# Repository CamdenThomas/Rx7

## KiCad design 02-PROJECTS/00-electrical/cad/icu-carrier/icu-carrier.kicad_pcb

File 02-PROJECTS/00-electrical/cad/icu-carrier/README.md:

# ICU carrier — the KiCad project

*Rev 2026-09-12 (rev 0.02 of the sheet) · owns: what this KiCad project is for, what it may
claim, and how to start. The board's design is `../../data/icu_channels.csv` — that is the
record; this is a drawing of it. Read `../README.md` first: it is the fence.*

## Where it stands

**The schematic is drawn, all five blocks, and ERC is clean at zero errors and zero
warnings** (re-run on the Fedora machine 2026-09-22, after J5 got its real pads and the 5 V buck
was drawn in full from TI's datasheet: U1 LMR36015FSCQ-Q1 with L2, C20–C26 and R41–R43, F13). The next
step is the beginner guide, `../PCB-AND-3D-GUIDE.md`, step 1. Power, bus, the nine analog channels plus the illumination reference, both
pulse inputs, and the display-and-local block. About 200 symbols, 95 named nets.

**It has already earned its keep.** The first pass had **every BAT54S clamp wired
backwards** — anode to +3V3 and cathode to ground instead of the other way round. Drawn
that way the clamp catches nothing on either polarity and puts a diode path from +3V3 to
ground straight through the sender. The prose the record carries — *"→ 100 nF → BAT54S to
3V3 / GND"* — is completely correct and completely silent about direction, which is the
argument for the drawing made in `../README.md`, arriving on the first attempt. It is
fixed, it is checked mechanically now, and the sheet says out loud which way round it goes
and why.

## Why it exists

1. **To learn KiCad on something real.** A tutorial board teaches the keystrokes and
   nothing else. This one is already specified down to the resistor values, so the design
   work is done and the only thing left to learn is the tool. Whatever comes next that
   needs a PCB, the practice is already paid for.
2. **Because the analog front end cannot be reviewed as prose.** See `../README.md`.

## What it may and may not claim

**May:** how the parts on the carrier connect to each other — divider ratios, clamp
placement, the pull-up jumpers, the comparator's hysteresis network, decoupling, what
shares a rail, and what the ERC thinks of all of it.

**May not:** anything about the car, the harness, or the drops. `DP-ICU-A 1` and
`DP-ICU-B 4` appear here only as pins on the board edge; what is on the other side of them
belongs to `cavities.csv`. **If this schematic and the record disagree, the record is
right.**

**Two things this revision deliberately does not assert, and says so on the sheet:**

- **The Teensy pinout — asserted since 2026-09-22.** D-377 put every channel's Teensy pin in
  `icu_channels.teensy_pin`, so `J5` now carries the real Teensy 4.1 pad numbers (pad n = edge
  pin n, pad 1 = GND at the USB end) and the six power pins it had been missing — VIN on `+5V`,
  3V3 ×2 on `+3V3`, GND ×3 — along its bottom edge. Its footprint is
  `icu-carrier.pretty/Teensy41_Socket` (`confirm - not measured`). The SPI nets are named
  `SPI_*` now, not `QSPI_*` (D-377).
- **No module pin numbers.** The transceiver, the IMU, the radio and the BT817 header are
  functional blocks (the buck is not any more: it is the real 12-pin part, F13). Their pin *names* are real; their pin *numbers* are fixed
  against the actual parts at layout (`F2`).

**And R11 applies with full force:** none of this has been measured. A schematic that
passes ERC is internally consistent, not correct. The panel timings, the tach comparator's
real noise margin, and every sender curve are still unmeasured — drawing them neatly does
not close them. The sheet carries its own "what this sheet does not know" panel, and
`TARGET.md §6` is the same list.

## Scope: schematic yes, PCB not yet — superseded 2026-09-21

> **Layout is now in scope** (D-361): Camden asked for the full layout and 3D guide, and ICU
> layout was already his step `F2`. Follow `../PCB-AND-3D-GUIDE.md` Part A. The paragraph below
> is kept for why it used to say no. Its last point still stands: **fabricating** (ordering
> boards) is money with a lead time, and it stays Camden's.

Capture the schematic. Do not lay out a board until there is a reason to, and "I have a
schematic" is not one. The carrier can be protoboard for bring-up, and fabricating one is
a decision with a lead time, a cost and a revision cycle attached — which makes it **big**
by §3, so it is a block before any time goes into `.kicad_pcb`, not an assumption because
the file exists. There is no `.kicad_pcb` in this folder on purpose.

## Opening it

KiCad 10.0.6 is installed system-wide (`/usr/bin/kicad`, `/usr/bin/kicad-cli`). Open
`icu-carrier.kicad_pro` and the sheet is there — A0, five blocked-out areas. ERC was re-run on
this machine on 2026-09-22: 0 errors, 0 warnings.

**Every symbol it uses is in `icu-carrier.kicad_sym`, beside the project**, with a
`sym-lib-table` pointing at it. Nothing depends on which KiCad libraries happen to be
installed, so the sheet opens identically after a reinstall or a KiCad upgrade, and ERC has no
missing-library complaints to make.

## Checking it

```
kicad-cli sch erc icu-carrier.kicad_sch --severity-all -o icu-carrier-erc.rpt
kicad-cli sch export svg --no-background-color -o . icu-carrier.kicad_sch
```

ERC violations are errors, not suggestions — the same standing as a `check` refusal. The
report is gitignored; the **SVG is committed**, because an S-expression diff of coordinate
tuples cannot be reviewed by anyone, including you in three weeks. A PDF
(`kicad-cli sch export pdf`) is easier to read at a desk and is gitignored for the same
reason a second copy of any fact is: one picture in the repo, not two.

## Files

| File | What |
|---|---|
| `icu-carrier.kicad_pro` · `.kicad_sch` | the project and the schematic |
| `icu-carrier.kicad_sym` · `sym-lib-table` | every symbol used, kept with the project |
| `icu-carrier.svg` | the committed picture — the reviewable form of a change |
| `CONVENTIONS.md` | how to draw it so it stays reviewable |
| `TARGET.md` | what has to be on the sheet, from `icu_channels.csv` — a snapshot, not a link |

`.kicad_prl`, `*-backups/`, `*.kicad_sch-bak`, autosaves, the ERC report, the netlist and
the PDF are gitignored.

## What to draw next

Nothing, until something in the record changes or a bench result arrives. The open ends
are all measurements, not drawings:

- `Q-308` picks an oil-temperature sender and IC07's pull-up stops being a question mark.
- `V-084` settles the BT817's pixel clock and sync polarity against the real panel.
- `D-261`'s three-point sender reads make IC01 and IC03 curves rather than dividers.
- The tach front end is a bench result: LM393 or H11L1, and the hysteresis values on this
  sheet are a proposal derived here, not a fact from the record.
- `F2` lays out the carrier — and only then do module and socket pin numbers mean anything.

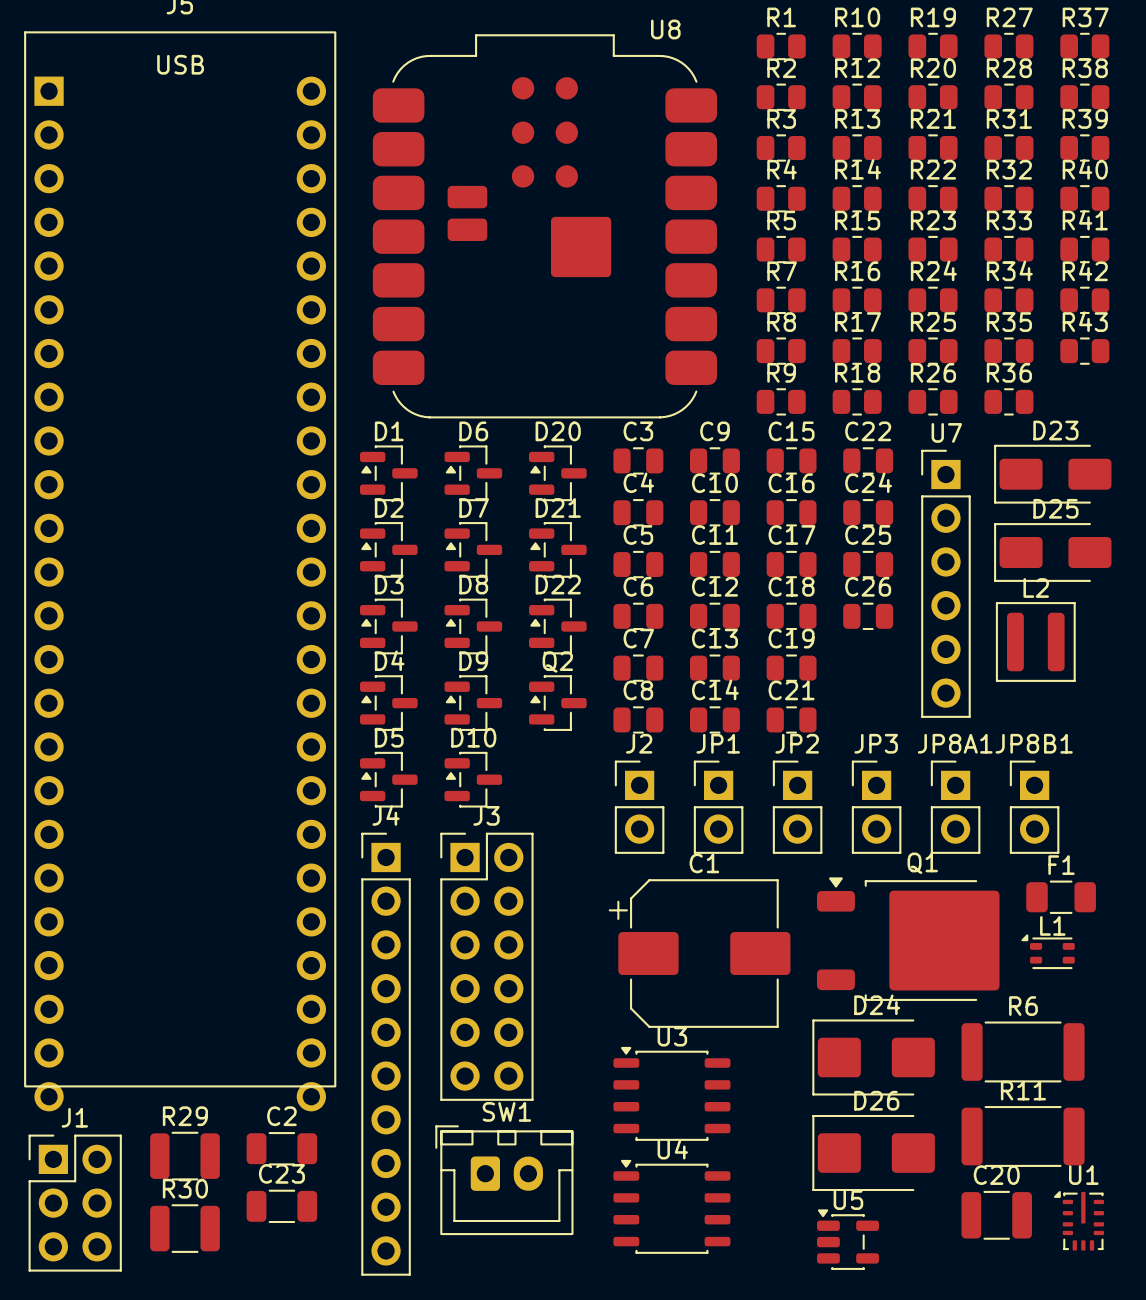
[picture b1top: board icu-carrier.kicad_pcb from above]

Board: 2 copper layers, 108 parts (0 on the bottom side), 73 nets, no tracks yet.

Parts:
C1: 100u 63V; CP_Elec_8x10
C2: 22u 16V; C_1206_3216Metric
C3, C4, C5, C6, C7, C8, C9, C10, C11, C12, C13, C14, C15, C16, C17, C18: 100n; C_0805_2012Metric
C19: 10u; C_0805_2012Metric
C20: 4.7u 100V X7R; C_1210_3225Metric
C21, C22: 220n 100V; C_0805_2012Metric
C23: 22u 10V X7R; C_1206_3216Metric
C24: 100n 16V; C_0805_2012Metric
C25: 1u 16V; C_0805_2012Metric
C26: 20p C0G; C_0805_2012Metric
D1, D2, D3, D4, D5, D6, D7, D8, D9, D10, D21, D22: BAT54S; SOT-23
D20: BZX84C5V1; SOT-23
D23, D25: SS34; D_SMA
D24, D26: SMBJ33A; D_SMB
F1: 4 A; Fuse_1206_3216Metric
J1: DT13-06PA; PinHeader_2x03_P2.54mm_Vertical
J2: backlight out; PinHeader_1x02_P2.54mm_Vertical
J3: DT13-12PA; PinHeader_2x06_P2.54mm_Vertical
J4: BT817 EVE bridge header; PinHeader_1x10_P2.54mm_Vertical
J5: Teensy 4.1 socket - 2 x 24 female headers (D-259); Teensy41_Socket
JP1: J1 FITTED; PinHeader_1x02_P2.54mm_Vertical
JP2: J3 FITTED; PinHeader_1x02_P2.54mm_Vertical
JP3: J7 NOT FITTED; PinHeader_1x02_P2.54mm_Vertical
JP8A1: J8A open collector; PinHeader_1x02_P2.54mm_Vertical
JP8B1: J8B push-pull; PinHeader_1x02_P2.54mm_Vertical
L1: common-mode choke - DNP; L_CommonModeChoke_Coilank_ACM2012
L2: 2.2u XAL4020-222; L_Coilcraft_XAL4020-XXX
Q1: SQD50P06 class, >= 60 V; TO-252-2
Q2: MMBT3904; SOT-23
R1, R3, R5, R8, R10, R13, R15, R17, R20, R22, R24, R26, R28, R34, R36, R38: 10k; R_0805_2012Metric
R2: 1k; R_0805_2012Metric
R4, R43: 100k; R_0805_2012Metric
R6, R11: 100R 1W; R_2512_6332Metric
R7, R9, R12, R19: 15k; R_0805_2012Metric
R14, R16, R21, R23, R25, R27: 47k; R_0805_2012Metric
R18: 1k - 2.2k 1% ?; R_0805_2012Metric
R29, R30: 100k 0.5W; R_1210_3225Metric
R31: 39k; R_0805_2012Metric
R32: 12k; R_0805_2012Metric
R33: 1.2M; R_0805_2012Metric
R35, R37, R39, R40: 4.7k; R_0805_2012Metric
R41: 100k 1%; R_0805_2012Metric
R42: 24.9k 1%; R_0805_2012Metric
SW1: IC22; JST_XH_B2B-XH-A_1x02_P2.50mm_Vertical
U1: LMR36015FSCQ-Q1; Texas_RNX0012C_VQFN-14-11-1EP_2x3mm_P0.5mm_EP0.25x1.825mm
U3: TCAN1042HVDRQ1; JEITA_SOIC-8_3.9x4.9mm_P1.27mm
U4: LM393; JEITA_SOIC-8_3.9x4.9mm_P1.27mm
U5: 74LVC1G17; SOT-23-5
U7: LSM6DSO / ICM-42688-P; PinHeader_1x06_P2.54mm_Vertical
U8: XIAO ESP32C3; MCU_Seeed_ESP32C3

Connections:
+3V3: C4.1, C16.1, C18.1, D1.2 (K), D2.2 (K), D3.2 (K), D4.2 (K), D5.2 (K), D6.2 (K), D7.2 (K), D8.2 (K), D9.2 (K), D10.2 (K), D21.2 (K), D22.2 (K), J4.1 (3V3), J5.15 (3V3), J5.46 (3V3), JP8A1.1, R34.1, R38.1, R39.1, R40.1, R43.1, U3.5 (VIO), U5.5 (VCC), U7.1 (VDD)
+5V: C2.1, C3.1, C15.1, C19.1, C23.1, C26.1, J5.48 (VIN), L2.2, R6.1, R11.1, R18.1, R31.1, R41.1, U3.3 (VCC), U4.8 (V+), U8.1 (5V)
+12V_BL: D25.1 (K), D26.2 (A2), F1.2
+12V_BL_SW: J2.1, Q1.2 (D)
+12V_LOGIC: C1.1, C20.1, C21.1, C22.1, D23.1 (K), D24.2 (A2), U1.2 (VIN), U1.9 (EN), U1.10 (VIN)
/BL_EN: J5.28 (BL_EN), R3.1, R4.1
/BT817_INT: J4.9 (INT), J5.16 (BT817_INT)
/BT817_PD: J4.10 (PD), J5.11 (BT817_PD)
/BT_IO2: J4.7 (QSPI_IO2), J5.18 (BT_IO2)
/BT_IO3: J4.8 (QSPI_IO3), J5.19 (BT_IO3)
/BUCK_BOOT: C24.1, U1.4 (BOOT)
/BUCK_FB: C26.2, R41.2, R42.1, U1.7 (FB)
/BUCK_SW: C24.2, L2.1, U1.3 (NC), U1.12 (SW)
/BUCK_VCC: C25.1, U1.5 (VCC)
/CAN2H_J: J1.4, L1.2
/CAN2L_J: J1.5, L1.4
/CAN_RXD: J5.45 (CAN_RXD), U3.4 (RXD)
/CAN_STB: J5.24 (CAN_STB), R5.1, U3.8 (STB)
/CAN_TXD: J5.44 (CAN_TXD), U3.1 (TXD)
/I2C_SCL: J5.41 (I2C_SCL), R39.2, U7.3 (SCL)
/I2C_SDA: J5.40 (I2C_SDA), R40.2, U7.4 (SDA)
/IC01_ADC: C5.1, D1.3 (COM), J5.36 (IC01_ADC), R7.2, R8.1
/IC02_ADC: C6.1, D2.3 (COM), J5.37 (IC02_ADC), R9.2, R10.1
/IC03_ADC: C7.1, D3.3 (COM), J5.38 (IC03_ADC), R12.2, R13.1
/IC04_CAP: J5.4 (IC04_CAP), R33.1, R34.2, U4.1
/IC05_ADC: C8.1, D4.3 (COM), J5.39 (IC05_ADC), R14.2, R15.1
/IC06_DIG: C9.1, D5.3 (COM), J5.20 (IC06_DIG), R16.2, R17.1
/IC07_ADC: C10.1, D6.3 (COM), J5.42 (IC07_ADC), R19.2, R20.1
/IC08_CAP: J5.5 (IC08_CAP), U5.4
/IC09_DIG: C11.1, D7.3 (COM), J5.21 (IC09_DIG), R21.2, R22.1
/IC10_DIG: C12.1, D8.3 (COM), J5.22 (IC10_DIG), R23.2, R24.1
/IC11_DIG: C13.1, D9.3 (COM), J5.23 (IC11_DIG), R25.2, R26.1
/IC14_ADC: C14.1, D10.3 (COM), J5.43 (IC14_ADC), R27.2, R28.1
/IC14_IN: J1.2, R27.1
/ICU_B1: J3.1, JP1.1, R7.1
/ICU_B2: J3.2, R9.1
/ICU_B3: J3.3, JP2.1, R12.1
/ICU_B4: J3.4, R29.2
/ICU_B5: J3.5, R14.1
/ICU_B6: J3.6, R16.1
/ICU_B7: J3.7, JP3.1, R19.1
/ICU_B8: D22.3 (COM), J3.8, JP8B1.1, R35.2, R36.2, R37.1, U5.2
/ICU_B10: J3.10, R21.1
/ICU_B11: J3.11, R23.1
/ICU_B12: J3.12, R25.1
/IMU_INT: J5.25 (IMU_INT), U7.5 (INT1)
/PAGE_BTN: C17.1, J5.17 (PAGE_BTN), R38.2, SW1.2
/PG_5V: J5.29 (PG_5V), R43.2, U1.8 (PG)
/RADIO_BOOT: J5.27 (RADIO_BOOT), U8.7 (BOOT)
/RADIO_EN: J5.26 (RADIO_EN), U8.6 (EN)
/RADIO_RX: J5.10 (RADIO_RX), U8.5 (RX)
/RADIO_TX: J5.9 (RADIO_TX), U8.4 (TX)
/SPI_CS: J4.3 (QSPI_CS), J5.12 (SPI_CS)
/SPI_MISO: J4.6 (QSPI_IO1), J5.14 (SPI_MISO)
/SPI_MOSI: J4.5 (QSPI_IO0), J5.13 (SPI_MOSI)
/SPI_SCK: J4.4 (QSPI_SCK), J5.35 (SPI_SCK)
GND: C1.2, C2.2, C3.2, C4.2, C5.2, C6.2, C7.2, C8.2, C9.2, C10.2, C11.2, C12.2, C13.2, C14.2, C15.2, C16.2, C17.2, C18.2, C19.2, C20.2, C21.2, C22.2, C23.2, C25.2, D1.1 (A), D2.1 (A), D3.1 (A), D4.1 (A), D5.1 (A), D6.1 (A), D7.1 (A), D8.1 (A), D9.1 (A), D10.1 (A), D20.1 (K), D21.1 (A), D22.1 (A), D24.1 (A1), D26.1 (A1), J1.3, J2.2, J4.2 (GND), J5.1 (GND), J5.34 (GND), J5.47 (GND), Q2.2 (E), R4.2, R5.2, R8.2, R10.2, R13.2, R15.2, R17.2, R20.2, R22.2, R24.2, R26.2, R28.2, R32.2, R37.2, R42.2, SW1.1, U1.1 (PGND), U1.6 (AGND), U1.11 (PGND), U3.2 (GND), U4.4 (V-), U4.5 (+), U4.6 (-), U5.3 (GND), U7.2 (GND), U8.2 (GND)
unnamed: D20.2 (A), D21.3 (COM), R30.1, R33.2, U4.3 (+)
unnamed: D23.2 (A), J1.1
unnamed: D25.2 (A), J1.6
unnamed: JP1.2, R6.2
unnamed: JP2.2, R11.2
unnamed: JP3.2, R18.2
unnamed: JP8A1.2, R35.1
unnamed: JP8B1.2, R36.1
unnamed: Q1.1 (G), R1.2, R2.1
unnamed: F1.1, Q1.3 (S), R1.1
unnamed: Q2.1 (B), R3.2
unnamed: Q2.3 (C), R2.2
unnamed: R29.1, R30.2
unnamed: L1.1, U3.7 (CANH)
unnamed: L1.3, U3.6 (CANL)
unnamed: R31.2, R32.1, U4.2 (-)

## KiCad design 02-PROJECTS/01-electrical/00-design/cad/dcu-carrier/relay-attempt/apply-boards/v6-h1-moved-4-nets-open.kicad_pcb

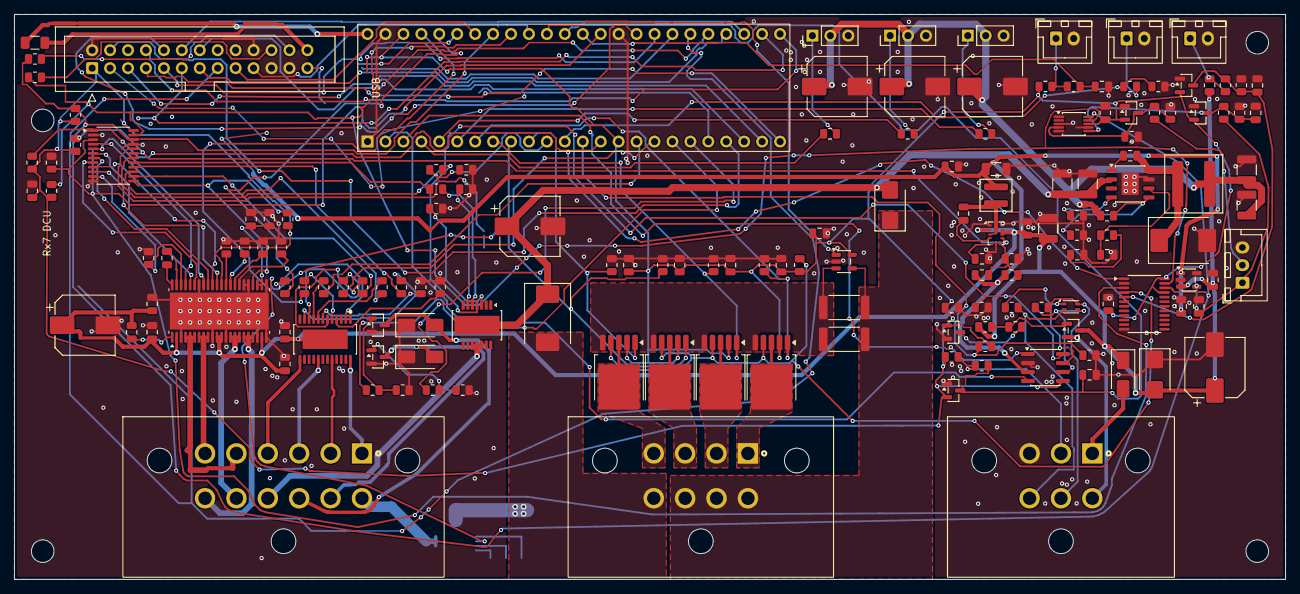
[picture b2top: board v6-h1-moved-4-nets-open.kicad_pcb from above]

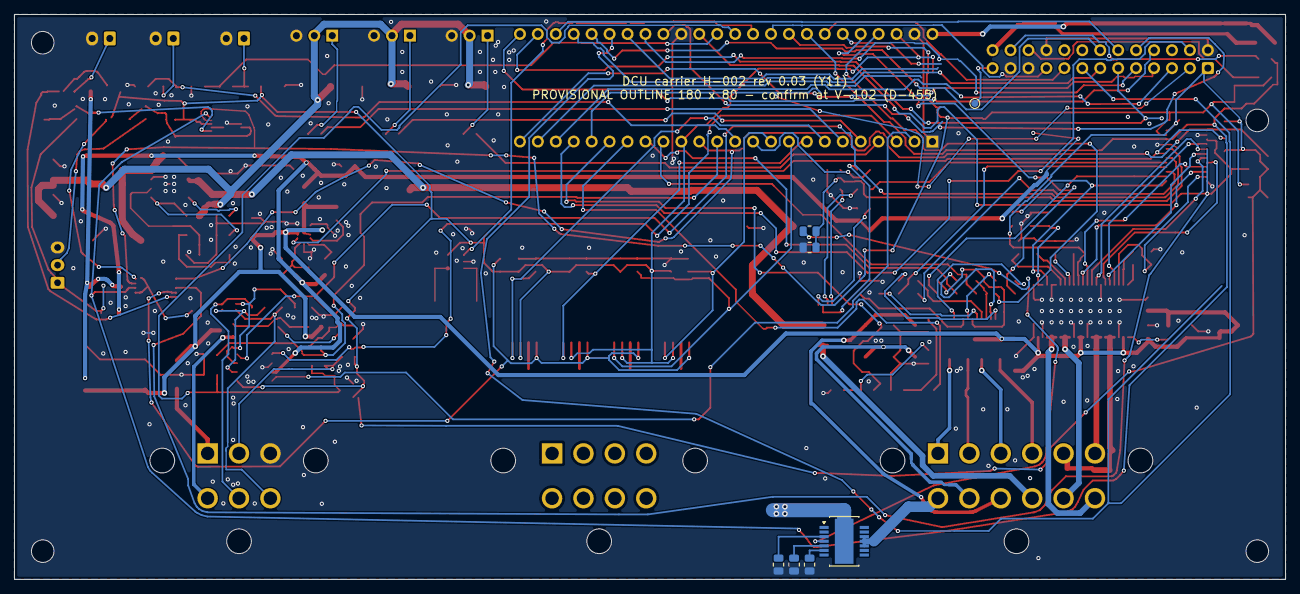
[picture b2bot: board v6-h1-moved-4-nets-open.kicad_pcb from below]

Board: 2 copper layers, 180.0 x 80.0 mm, 169 parts (7 on the bottom side), 146 nets.

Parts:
C1, C8, C29: 100u 63V; CP_Elec_8x10
C2, C9, C10: 4.7u 100V X7R; C_1210_3225Metric
C3: 220n 100V; C_0805_2012Metric
C4, C11: 100n 16V; C_0805_2012Metric
C5: 1u 16V; C_0805_2012Metric
C6: 20p C0G; C_0805_2012Metric
C7: 22u 16V X7R; C_1206_3216Metric
C12: 4.7n confirm; C_0805_2012Metric
C13: 47p confirm; C_0805_2012Metric
C14, C15: 47u 10V X7R; C_1210_3225Metric
C16, C17, C18, C19, C20, C21, C22, C23, C24, C34, C41, C43, C44, C45: 100n; C_0805_2012Metric
C25, C30: 100n 100V; C_0805_2012Metric
C26: 1u 25V confirm; C_0805_2012Metric
C27: 22n 100V confirm; C_0805_2012Metric
C28: 1u; C_0805_2012Metric
C31, C32, C33: 470u 10V; CP_Elec_8x10
C35: 100n at pin 25 (VCC); C_0805_2012Metric
C36: 10n 100V VM-PGND1 (TI 6-1); C_0805_2012Metric
C37: 10n 100V VM-PGND3 (TI 6-1); C_0805_2012Metric
C38: 100n U13 VCC; C_0805_2012Metric
C39: 100n U15 VDD; C_0805_2012Metric
C40: 1u 50V; C_0805_2012Metric
C42: 2.2u; C_0805_2012Metric
D1: SS34; D_SMA
D2, D4: SMBJ33A; D_SMB
D3: B560C 60V 5A - confirm; D_SMC
D5: B560C 60V 5A catch; D_SMC
D6, D9, D10, D11: BAT54S; SOT-23
D7, D8: SMAJ40A confirm; D_SMA
F1: PTC 0.5A hold 1206 - confirm; Fuse_1206_3216Metric
H1, H2, H3, H4: M3; MountingHole_3.2mm_M3
J1: DP-DCU DT13-06PA; DT13-06PA
J2: DP-DCU-C DT13-08PA; DT13-08PA
J3: cabin NTC lead; JST_XH_B2B-XH-A_1x02_P2.50mm_Vertical
J4: panel ribbon 2x13 IDC, keyed; IDC-Header_2x13_P2.54mm_Vertical
J5: blower pigtail; JST_XH_B2B-XH-A_1x02_P2.50mm_Vertical
J6, J7, J8: servo header; PinHeader_1x03_P2.54mm_Vertical
J9: DP-DCU-B DT13-12PA; DT13-12PA
J10: Teensy 4.1 socket - 2 x 24 female headers; Teensy41_Socket
J11: A/C pressure transducer lead - PLACEHOLDER; JST_XH_B3B-XH-A_1x03_P2.50mm_Vertical
J12: radar alert lead - PLACEHOLDER; JST_XH_B2B-XH-A_1x02_P2.50mm_Vertical
L1: 2.2u XAL4020-222; L_Coilcraft_XAL4020-XXX
L2: 6.8u Isat >= 7 A - confirm; L_Coilcraft_XAL7030-682
L3: common-mode choke - DNP, fit only with R instead 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; L_CommonModeChoke_Coilank_ACM2012
Q1, Q2: PMV37ENEA; SOT-23
Q3: SQ2351ES class, >= 40 V confirm; SOT-23
Q4: MMBT3904; SOT-23
R1: 100k 1%; R_0805_2012Metric
R2: 24.9k 1%; R_0805_2012Metric
R3, R45: 100k; R_0805_2012Metric
R4: 243k 1% ~400 kHz; R_0805_2012Metric
R5: 52.3k 1%; R_0805_2012Metric
R6, R11, R13: 10k 1%; R_0805_2012Metric
R7: 16.9k confirm; R_0805_2012Metric
R8, R12, R14, R36, R39, R41, R42, R44, R53, R64, R66, R68: 10k; R_0805_2012Metric
R9, R10: 0R fitted in place of the choke; R_0805_2012Metric
R15, R16: 10m 2512 3W; R_2512_6332Metric
R17, R18, R19, R20, R22, R60: 10k off at reset; R_0805_2012Metric
R21, R23, R26, R27, R28, R29, R30, R31, R32, R51, R52, R59: 4.7k; R_0805_2012Metric
R24: 1.2k IS unread - no ADC pin left; R_0805_2012Metric
R25, R34, R63: 47R PROFET ground; R_0805_2012Metric
R33, R62: 1.2k IS unread; R_0805_2012Metric
R35: 100k asleep at reset; R_0805_2012Metric
R37, R55, R56, R57: 1.5k confirm vs stall (W-332); R_0805_2012Metric
R38, R40, R46, R71, R72: 100R; R_0805_2012Metric
R43: 1k; R_0805_2012Metric
R47: 10k off through a reset; R_0805_2012Metric
R48, R49, R50: 330R; R_0805_2012Metric
R54: 10k held in reset until the firmware lets go; R_0805_2012Metric
R58: 10k STATUS pull-up (BTS3011TE p.40); R_0805_2012Metric
R61: 4.7k DEN low; R_0805_2012Metric
R65, R67: 20k; R_0805_2012Metric
R69: 47k; R_0805_2012Metric
R70: 22k; R_0805_2012Metric
TP1: ribbon spare; TestPoint_Pad_D1.0mm
U1: LMR36015FSCQ-Q1; Texas_RNX0012C_VQFN-14-11-1EP_2x3mm_P0.5mm_EP0.25x1.825mm
U2: TPS54560B-Q1; HSOP-8-1EP_3.9x4.9mm_P1.27mm_EP2.41x3.1mm
U3: TCAN1042HVDRQ1; SOIC-8_3.9x4.9mm_P1.27mm
U4: INA180A1; SOT-23-5
U5, U6, U7, U8: BTS3011TE; TO-252-5_TabPin6
U9, U14: BTT6050-1ERA; Infineon_PG-TSDSO-14-22
U10: BTT6200-4ESA; Infineon_PG-TSDSO-24-21
U11: DRV8962-Q1; HTSSOP-44-1EP_6.1x14mm_P0.635mm_EP5.2x14mm_Mask4.31x8.26mm
U12, U13: TCA9539-Q1; TSSOP-24_4.4x7.8mm_P0.65mm
U15: ADS1115-Q1; MSOP-10_3x3mm_P0.5mm
U16: TPS7B4250-Q1; SOT-23-5

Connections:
+3V3: C17.1, C20.1, C21.1, C22.1, C23.1, C24.1, C34.1, C38.1, C39.1, D6.2, D9.2, D10.2, D11.2, J4.1, J10.15, J10.46, R3.1, R11.1, R13.1, R36.1, R51.1, R52.1, R53.1, R58.1, U3.5, U4.5, U5.2, U6.2, U7.2, U8.2, U11.33, U12.24, U13.21, U13.24, U15.8
+5V: C6.1, C7.1, C16.1, C41.1, F1.1, J10.48, L1.2, R1.1, U3.3, U16.1
+5V_SERVO: C14.1, C15.1, C31.1, C32.1, C33.1, J6.2, J7.2, J8.2, L2.2, R5.1
+12V_CMF: C8.1, C9.1, C10.1, D3.1, D4.2, U2.2, U9.TAB
+12V_LOGIC: C1.1, C2.1, C3.1, C25.1, C26.2, C29.1, C30.1, C36.1, C37.1, C40.1, D1.1, D2.2, Q3.3, R42.1, R68.1, U1.2, U1.9, U1.10, U10.TAB, U11.2, U11.11, U11.12, U11.21, U16.3
/+5V_PNL: F1.2, J4.26
/AC_CLUTCH: J9.12, U14.10, U14.11, U14.12
/AC_CLUTCH_CMD: R59.1, R60.1, U12.20
/AC_DEN_R: R61.1, U14.5
/AC_GND: R63.1, U14.3
/AC_IN: R59.2, U14.4
/AC_IS: R62.1, U14.6
/AC_PRESS_ADC: C43.1, D9.3, R64.2, R65.1, U15.4
/AC_PRESS_IN: J11.2, R64.1
/BLOWER_PWM: J5.1, R46.2
/BLOWER_T: J10.12, R46.1, R47.1
/BUCK_BOOT: C4.1, U1.4
/BUCK_FB: C6.2, R1.2, R2.1, U1.7
/BUCK_SW: C4.2, L1.1, U1.3, U1.12
/BUCK_VCC: C5.1, U1.5
/CABIN_ADC: C18.1, J10.36, R12.2
/CANH_J: J1.4, L3.2, R9.2
/CANH_U: L3.1, R9.1, U3.7
/CANL_J: J1.5, L3.4, R10.2
/CANL_U: L3.3, R10.1, U3.6
/CAN_RXD: J10.2, U3.4
/CAN_STB: R8.1, U3.8, U12.18
/CAN_TXD: J10.3, U3.1
/CMF_RTN: R15.1, R16.1, U4.3, U5.5, U6.5, U7.5, U8.5
/COL1: J4.6, J10.23
/COL2: J4.7, J10.24
/COL3: J4.8, J10.25
/CUR_ADC: J10.38, U4.1
/ENC_FAN_A: J4.9, J10.32
/ENC_FAN_B: J4.10, J10.33
/ENC_SEAT_DRV_A: J4.13, J10.28
/ENC_SEAT_DRV_B: J4.14, J10.29
/ENC_SEAT_PASS_A: J4.15, J10.30
/ENC_SEAT_PASS_B: J4.16, J10.31
/ENC_TEMP_A: J4.11, J10.26
/ENC_TEMP_B: J4.12, J10.27
/EXP_INT: J10.14, R53.2, U12.1, U13.1
/EXP_RESET: J10.35, R54.1, U12.3, U13.3
/I2C_SCL: J10.41, R52.2, R72.1, U12.22, U13.22, U15.10
/I2C_SDA: J10.40, R51.2, R71.1, U12.23, U13.23, U15.9
/JOY_PRESS: J4.19, J10.39
/JOY_X: J4.17, J10.42
/JOY_Y: J4.18, J10.43
/MH_DEN: R23.1, U12.17
/MH_DEN_R: R23.2, U9.5
/MH_GND: R25.1, U9.3
/MH_IN: R21.2, U9.4
/MH_IN_T: J10.11, R21.1, R22.1
/MH_IS: R24.1, U9.6
/MIRROR_HEAT: J9.9, U9.10, U9.11, U9.12
/MIR_CLUTCH: J9.8, U11.14, U11.15, U11.16
/MIR_COM: J9.5, U11.4, U11.5, U11.6
/MIR_CPH: C27.1, U11.44
/MIR_CPL: C27.2, U11.43
/MIR_DVDD: C28.1, C35.1, U11.24, U11.25
/MIR_EN1: U11.37, U12.5
/MIR_EN2: U11.36, U12.7
/MIR_EN3: U11.35, U12.9
/MIR_EN4: U11.34, U12.10
/MIR_IN1: U11.41, U12.4
/MIR_IN2: U11.40, U12.6
/MIR_IN3: U11.39, U12.8
/MIR_IPROPI1: R37.1, U11.32
/MIR_IPROPI2: R55.1, U11.31
/MIR_IPROPI3: R56.1, U11.30
/MIR_IPROPI4: R57.1, U11.29
/MIR_L: J9.6, U11.7, U11.8, U11.9
/MIR_R: J9.7, U11.17, U11.18, U11.19
/MIR_VCP: C26.1, U11.1
/MIR_nFAULT: R36.2, U11.26, U12.13
/MIR_nSLEEP: R35.1, U11.42, U12.11
/NTC_CABIN: J3.1, R11.2, R12.1
/OAT_ADC: C19.1, D6.3, J10.37, R14.2
/OAT_IN: J1.2, R13.2, R14.1
/PG_5V: R3.2, U1.8, U12.19
/PNL_SCL: J4.24, R72.2
/PNL_SDA: J4.22, R71.2
/RADAR_ALERT: C45.1, D11.3, R69.2, R70.1, U13.5
/RADAR_IN: J12.1, R68.2, R69.1
/REL_FUEL: D8.2, J9.11, Q2.3
/REL_FUEL_G: Q2.1, R40.2, R41.1
/REL_FUEL_T: J10.19, R40.1
/REL_HATCH: D7.2, J9.10, Q1.3
/REL_HATCH_G: Q1.1, R38.2, R39.1
/REL_HATCH_T: J10.18, R38.1
/ROW1: J4.3, J10.20
/ROW2: J4.4, J10.21
/ROW3: J4.5, J10.22
/SC_DRV_IN: J10.9, R19.1, U7.1
/SC_DRV_RTN: J2.3, U7.3, U7.6
/SC_PASS_IN: J10.10, R20.1, U8.1
/SC_PASS_RTN: J2.4, U8.3, U8.6
/SEAT_STATUS: R58.2, U5.4, U6.4, U7.4, U8.4, U13.4
/SENS_5V: C42.1, J11.1, R66.1, U16.4
/SENS_5V_ADC: C44.1, D10.3, R66.2, R67.1, U15.6
/SH_DRV_IN: J10.7, R17.1, U5.1
/SH_DRV_RTN: J2.1, U5.3, U5.6
/SH_PASS_IN: J10.8, R18.1, U6.1
/SH_PASS_RTN: J2.2, U6.3, U6.6
/SPARE: J4.25, TP1.1
/SRV_BLEND: J7.1, R49.2
/SRV_BLEND_T: J10.5, R49.1
/SRV_BOOT: C11.1, U2.1
/SRV_CC: C12.1, R7.2
/SRV_COMP: C13.1, R7.1, U2.6
/SRV_FB: R5.2, R6.1, U2.5
/SRV_MODE: J6.1, R48.2
/SRV_MODE_T: J10.4, R48.1
/SRV_RECIRC: J8.1, R50.2
/SRV_RECIRC_T: J10.6, R50.1
/SRV_RT: R4.1, U2.4
/SRV_SW: C11.2, D5.1, L2.1, U2.8
/V12C_RAW: D3.2, J2.5, U14.TAB
/V12L_RAW: D1.2, J1.1
/WAKE_B: Q4.1, R44.2
/WAKE_C: Q4.3, R43.2
/WAKE_G: Q3.1, R42.2, R43.1
/WAKE_OUT: J1.6, Q3.2
/WAKE_T: J10.13, R44.1, R45.1
/WIN_DEN: R30.1, U12.14
/WIN_DEN_R: R30.2, U10.6
/WIN_DRV_DN: J9.2, U10.20
/WIN_DRV_UP: J9.1, U10.24
/WIN_DSEL0: R31.1, U12.15
/WIN_DSEL0_R: R31.2, U10.8
/WIN_DSEL1: R32.1, U12.16
/WIN_DSEL1_R: R32.2, U10.11
/WIN_GND: R34.1, U10.4
/WIN_IN0: J10.44, R26.1
/WIN_IN0_R: R26.2, U10.2
/WIN_IN1: J10.45, R27.1
/WIN_IN1_R: R27.2, U10.5
/WIN_IN2: J10.16, R28.1
/WIN_IN2_R: R28.2, U10.9
/WIN_IN3: J10.17, R29.1
/WIN_IN3_R: R29.2, U10.10
/WIN_IS: R33.1, U10.7
/WIN_PASS_DN: J9.4, U10.13
/WIN_PASS_UP: J9.3, U10.17
GND: C1.2, C2.2, C3.2, C5.2, C7.2, C8.2, C9.2, C10.2, C12.2, C13.2, C14.2, C15.2, C16.2, C17.2, C18.2, C19.2, C20.2, C21.2, C22.2, C23.2, C24.2, C25.2, C28.2, C29.2, C30.2, C31.2, C32.2, C33.2, C34.2, C35.2, C36.2, C37.2, C38.2, C39.2, C40.2, C41.2, C42.2, C43.2, C44.2, C45.2, D2.1, D5.2, D6.1, D7.1, D8.1, D9.1, D10.1, D11.1, J1.3, J3.2, J4.2, J4.20, J4.21, J4.23, J5.2, J6.3, J7.3, J8.3, J10.1, J10.34, J10.47, J11.3, J12.2, Q1.2, Q2.2, Q4.2, R2.2, R4.2, R6.2, R8.2, R17.2, R18.2, R19.2, R20.2, R22.2, R24.2, R25.2, R33.2, R34.2, R35.2, R37.2, R39.2, R41.2, R45.2, R47.2, R54.2, R55.2, R56.2, R57.2, R60.2, R61.2, R62.2, R63.2, R65.2, R67.2, R70.2, U1.1, U1.6, U1.11, U2.7, U2.9, U3.2, U4.2, U11.3, U11.10, U11.13, U11.20, U11.22, U11.23, U11.27, U11.28, U11.38, U11.45, U12.2, U12.12, U12.21, U13.2, U13.12, U15.1, U15.3, U15.5, U15.7, U16.2, U16.5
PGND: D4.1, J2.6, J2.7, J2.8, R15.2, R16.2, U4.4

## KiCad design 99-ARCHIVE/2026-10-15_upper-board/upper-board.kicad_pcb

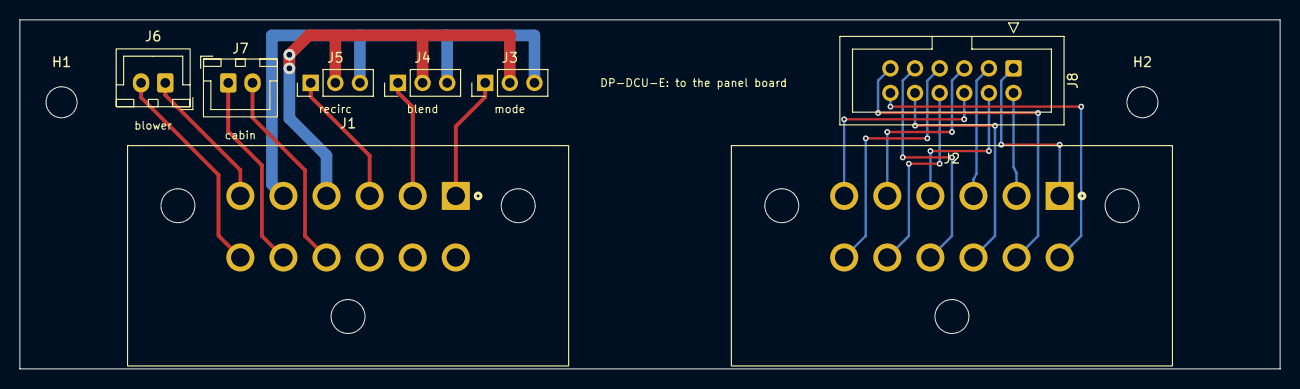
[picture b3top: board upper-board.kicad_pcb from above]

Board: 2 copper layers, 130.0 x 36.0 mm, 10 parts (0 on the bottom side), 21 nets.

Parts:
H1, H2: M3; MountingHole_3.2mm_M3
J1: DP-DCU-D DT13-12PA; DT13-12PA
J2: DP-DCU-E DT13-12PA; DT13-12PA
J3: to carrier J6 (mode servo); PinHeader_1x03_P2.54mm_Vertical
J4: to carrier J7 (blend servo); PinHeader_1x03_P2.54mm_Vertical
J5: to carrier J8 (recirculate servo); PinHeader_1x03_P2.54mm_Vertical
J6: to carrier J5 (blower duty); JST_XH_B2B-XH-A_1x02_P2.50mm_Vertical
J7: to carrier J3 (cabin NTC); JST_XH_B2B-XH-A_1x02_P2.50mm_Vertical
J8: to panel board plate header; IDC-Header_2x06_P2.54mm_Vertical

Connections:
/+3V3: J2.7, J8.7
/+5V_PNL: J2.12, J8.12
/+5V_SERVO: J1.4, J3.2, J4.2, J5.2
/AGND: J2.8, J8.8
/BLOWER_GND: J1.7, J6.2
/BLOWER_PWM: J1.6, J6.1
/COL2: J2.2, J8.2
/COL3: J2.3, J8.3
/GND: J2.11, J8.11
/JOY_PRESS: J2.6, J8.6
/JOY_X: J2.4, J8.4
/JOY_Y: J2.5, J8.5
/NTC_CABIN: J1.8, J7.1
/NTC_RET: J1.9, J7.2
/PNL_SCL: J2.10, J8.10
/PNL_SDA: J2.9, J8.9
/ROW1: J2.1, J8.1
/SERVO_GND: J1.5, J3.3, J4.3, J5.3
/SRV_BLEND: J1.2, J4.1
/SRV_MODE: J1.1, J3.1
/SRV_RECIRC: J1.3, J5.1

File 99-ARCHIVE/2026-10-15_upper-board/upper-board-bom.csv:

"Ref","Qty","Value","Footprint","DNP","Confirm"
"J1","1","DP-DCU-D  DT13-12PA","dcu-carrier:DT13-12PA","","pin numbering and the board edge 4 mm behind the flange are the carrier footprint's, confirm against the part (R11); X position from the climate-unit mock-up (Y14)"
"J2","1","DP-DCU-E  DT13-12PA","dcu-carrier:DT13-12PA","","pin numbering and the board edge 4 mm behind the flange are the carrier footprint's, confirm against the part (R11); X position from the climate-unit mock-up (Y14)"
"J3","1","to carrier J6 (mode servo)","Connector_PinHeader_2.54mm:PinHeader_1x03_P2.54mm_Vertical","","lead P196, length from the mock-up - confirm"
"J4","1","to carrier J7 (blend servo)","Connector_PinHeader_2.54mm:PinHeader_1x03_P2.54mm_Vertical","","lead P196, length from the mock-up - confirm"
"J5","1","to carrier J8 (recirculate servo)","Connector_PinHeader_2.54mm:PinHeader_1x03_P2.54mm_Vertical","","lead P196, length from the mock-up - confirm"
"J6","1","to carrier J5 (blower duty)","Connector_JST:JST_XH_B2B-XH-A_1x02_P2.50mm_Vertical","","lead P196, length from the mock-up - confirm"
"J7","1","to carrier J3 (cabin NTC)","Connector_JST:JST_XH_B2B-XH-A_1x02_P2.50mm_Vertical","","lead P196, length from the mock-up - confirm"
"J8","1","to panel board plate header","Connector_IDC:IDC-Header_2x06_P2.54mm_Vertical","","the panel board's plate header and its lead are Y20's - pin n is DP-DCU-E n"
